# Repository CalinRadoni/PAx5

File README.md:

# PAx5

## Note

This repository is archived because I am building a version with better integration
in the [pax-devices](https://github.com/CalinRadoni/pax-devices) repository.

## Description

__PAx5__ is a home automation platform designed to be secure, stable and powerful.

__#__ Hardware is centered around an ultra-low-power ARM Cortex-M0+ and a sub-GHz radio.

__#__ For security:
- AEAD (_Authenticated Encryption with Associated Data_) using the 128 or 256 bits key ChaCha20 algorithm (the _new_ protocol used in HTTPS, TLS, OpenSSL, ...);
- Unique, random, session keys;
- Communication protocol designed to withstand the known attacks against these type of communications.

__#__ Stability is increased with:
- the radio module's power is generally enough to not require intermediary routers;
- designed for high availability, redundant, gateways.

### Dependencies

CMSIS

### Hardware details

MCU: STM32L051xx
Radio: RFM69HW
SPI FLASH Memory

Rendering and pinouts are in `Docs/PAx5_Base` and in `Docs/PAx5_EnvSensor`.

Environment sensor rendering:

and a photo of the sensor and base board:

### Development Environment

Main tools used are:
- [KiCad EDA](http://kicad-pcb.org/)
- [Atollic TrueSTUDIO](https://atollic.com/truestudio/) Free Edition
- [Atom](https://atom.io/) editor

Supplementary tools:
- [Git](https://git-scm.com/)
- [STM32CubeMX](http://www.st.com/en/development-tools/stm32cubemx.html)
- [Inkscape](https://inkscape.org/en/)

### License

PAx5's software and documentation is released under the [GNU GPLv3](http://www.gnu.org/licenses/gpl-3.0.html) License. See the __LICENSE-GPLv3.txt__ file.

PAx5's hardware schematics are licensed under a [Creative Commons Attribution-ShareAlike 4.0 International License](http://creativecommons.org/licenses/by-sa/4.0/).
See the __LICENSE-CC-BY-SA-4.0.txt__ file.

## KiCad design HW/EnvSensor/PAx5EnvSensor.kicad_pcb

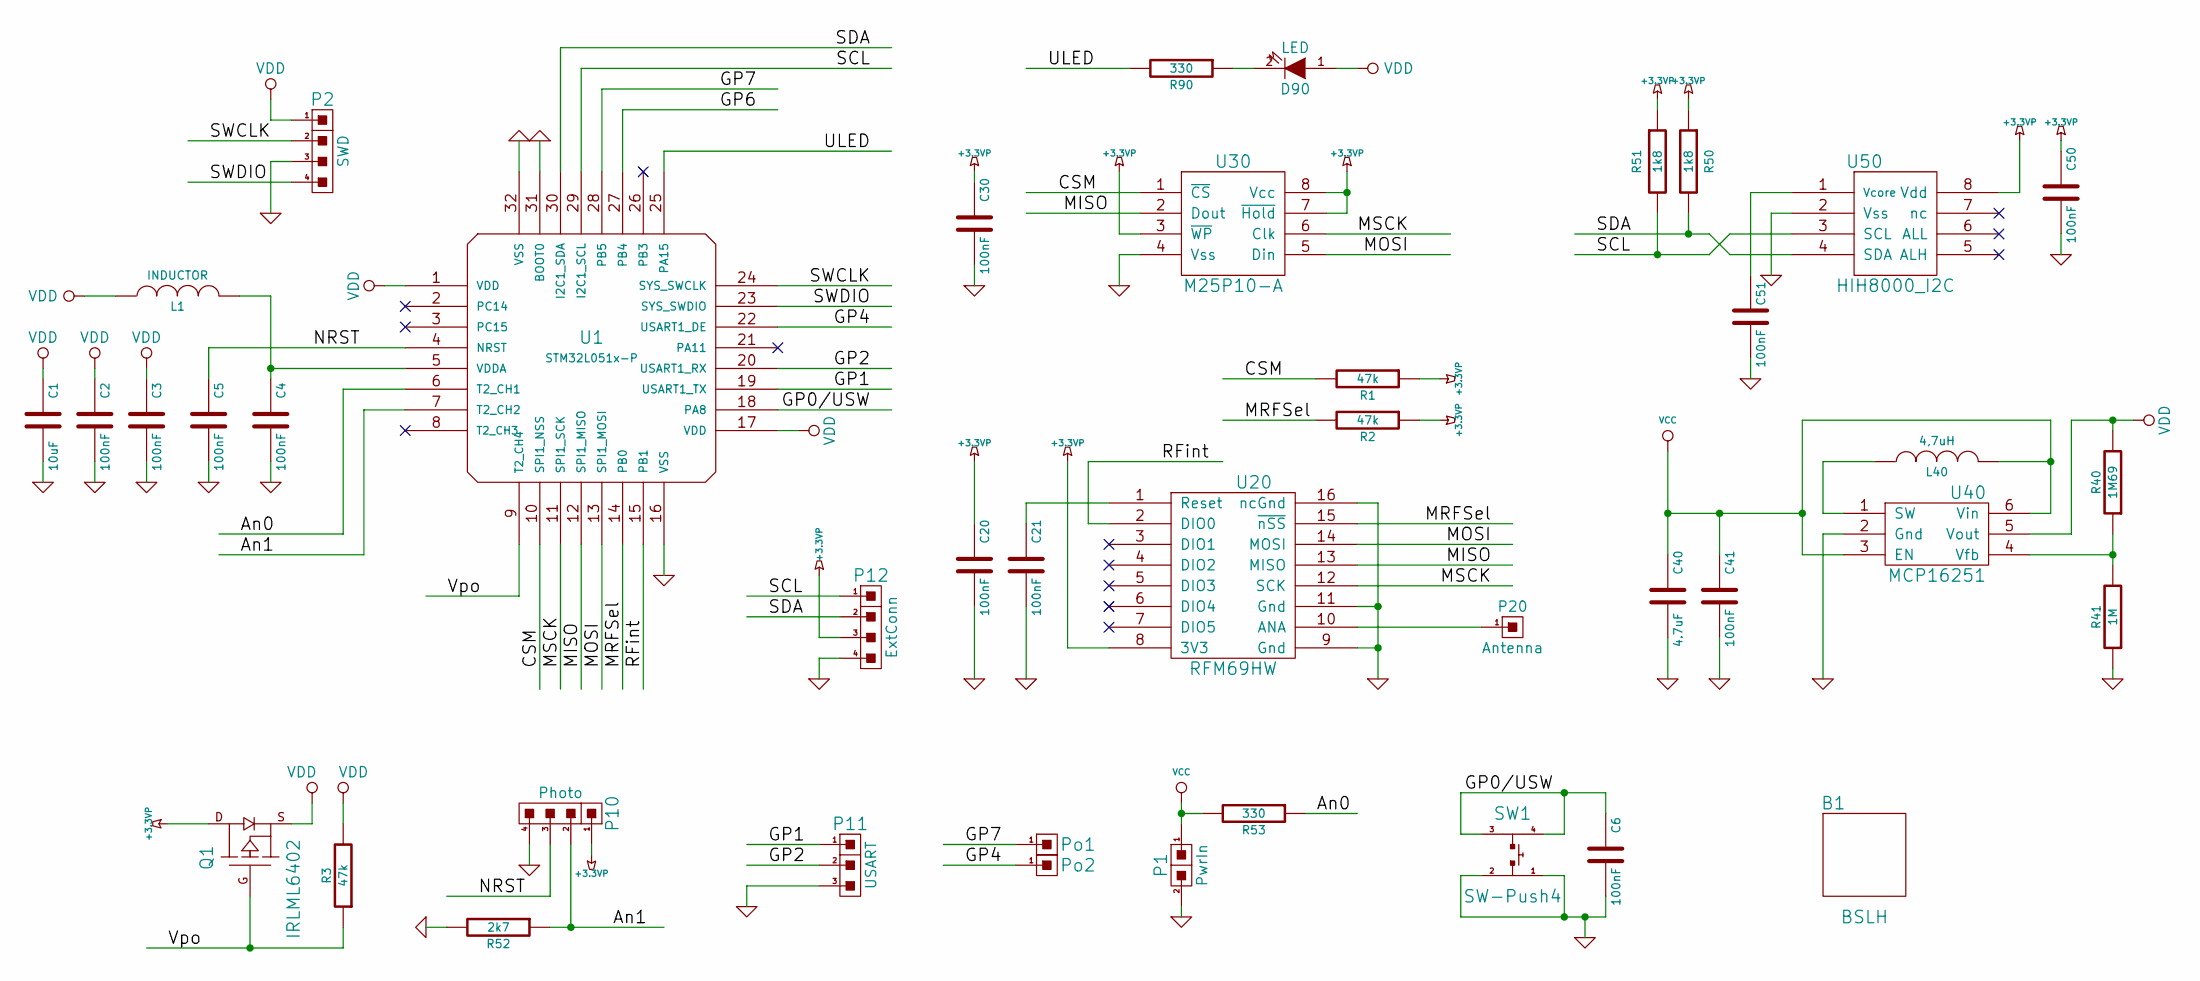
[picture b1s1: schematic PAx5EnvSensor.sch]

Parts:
B1: BSLH; Box-Sens-LH-NPTH
C1: 10uF; C_0805_HandSoldering
C2, C3, C4, C5, C6, C20, C21, C30, C41, C50, C51: 100nF; C_0805_HandSoldering
C40: 4.7uF; C_0805_HandSoldering
D90: LED; LED_1206_HandSoldering
L1: INDUCTOR; R_1206_HandSoldering
L40: 4,7uH; TYS50xx
P1: PwrIn; Pin_Header_Straight_1x02
P2: SWD; Pin_Header_Straight_1x04
P10: Photo; Pin_Header_Straight_1x04
P11: USART; Pin_Header_Straight_1x03
P12: ExtConn; Pin_Header_Straight_1x04
P20: Antenna; Pin_Header_Straight_1x01
Po1, Po2: PinTest-SMD
Q1: IRLML6402; SOT-23-calin
R1, R2, R3: 47k; R_0805_HandSoldering
R40: 1M69; R_0805_HandSoldering
R41: 1M; R_0805_HandSoldering
R50, R51: 1k8; R_0805_HandSoldering
R52: 2k7; R_1206_HandSoldering
R53: 330; R_0805_HandSoldering
R90: 330; R_1206_HandSoldering
SW1: SW-Push4; cSW-Push-4
U1: STM32L051x-P; cLQFP32-7-v2
U20: RFM69HW
U30: M25P10-A; SOIC-8-N
U40: MCP16251; SOT23-6
U50: HIH8000_I2C; HIH8000

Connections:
+3.3VP: C20.1, C30.1, C50.1, P10.1, P12.3, Q1.D, R1.1, R2.1, R50.1, R51.1, U20.8 (3V3), U30.3 (~WP), U30.7 (~Hold), U30.8 (Vcc), U50.8 (Vdd)
/An0: R53.1, U1.6 (T2_CH1)
/An1: P10.2, R52.1, U1.7 (T2_CH2)
/CSM: R1.2, U1.10 (SPI1_NSS), U30.1 (~CS)
/GP0/USW: C6.1, SW1.3, SW1.4, U1.18 (PA8)
/GP1: P11.1, U1.19 (USART1_TX)
/GP2: P11.2, U1.20 (USART1_RX)
/GP4: Po2.1, U1.22 (USART1_DE)
/GP7: Po1.1, U1.28 (PB5)
/MISO: U1.12 (SPI1_MISO), U20.13 (MISO), U30.2 (Dout)
/MOSI: U1.13 (SPI1_MOSI), U20.14 (MOSI), U30.5 (Din)
/MRFSel: R2.2, U1.14 (PB0), U20.15 (~nSS)
/MSCK: U1.11 (SPI1_SCK), U20.12 (SCK), U30.6 (Clk)
/NRST: C5.1, P10.3, U1.4 (NRST)
/RFint: U1.15 (PB1), U20.2 (DIO0)
/SCL: P12.1, R51.2, U1.29 (I2C1_SCL), U50.3 (SCL)
/SDA: P12.2, R50.2, U1.30 (I2C1_SDA), U50.4 (SDA)
/SWCLK: P2.2, U1.24 (SYS_SWCLK)
/SWDIO: P2.4, U1.23 (SYS_SWDIO)
/ULED: R90.2, U1.25 (PA15)
/Vpo: Q1.G, R3.1, U1.9 (T2_CH4)
GND: C1.2, C2.2, C3.2, C4.2, C5.2, C6.2, C20.2, C21.2, C30.2, C40.2, C41.2, C50.2, C51.2, P1.2, P2.3, P10.4, P11.3, P12.4, R41.1, R52.2, SW1.1, SW1.2, U1.16 (VSS), U1.31 (BOOT0), U1.32 (VSS), U20.9 (Gnd), U20.11 (Gnd), U20.16 (ncGnd), U30.4 (Vss), U40.2 (Gnd), U50.2 (Vss)
unnamed: C4.1, L1.2, U1.5 (VDDA)
unnamed: C21.1, U20.1 (Reset)
unnamed: C51.1, U50.1 (Vcore)
unnamed: D90.2 (K), R90.1
unnamed: L40.1, U40.1 (SW)
unnamed: P20.1, U20.10 (ANA)
unnamed: R40.1, R41.2, U40.4 (Vfb)
VCC: C40.1, C41.1, L40.2, P1.1, R53.2, U40.3 (EN), U40.6 (Vin)
VDD: C1.1, C2.1, C3.1, D90.1 (A), L1.1, P2.1, Q1.S, R3.2, R40.2, U1.1 (VDD), U1.17 (VDD), U40.5 (Vout)

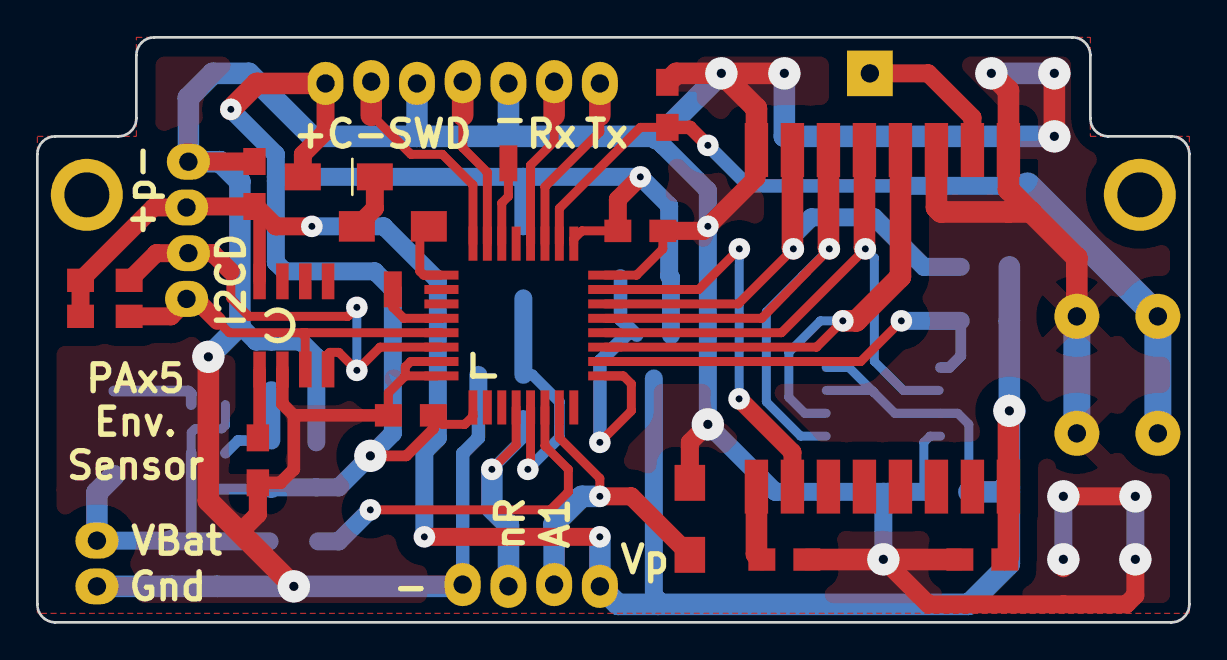
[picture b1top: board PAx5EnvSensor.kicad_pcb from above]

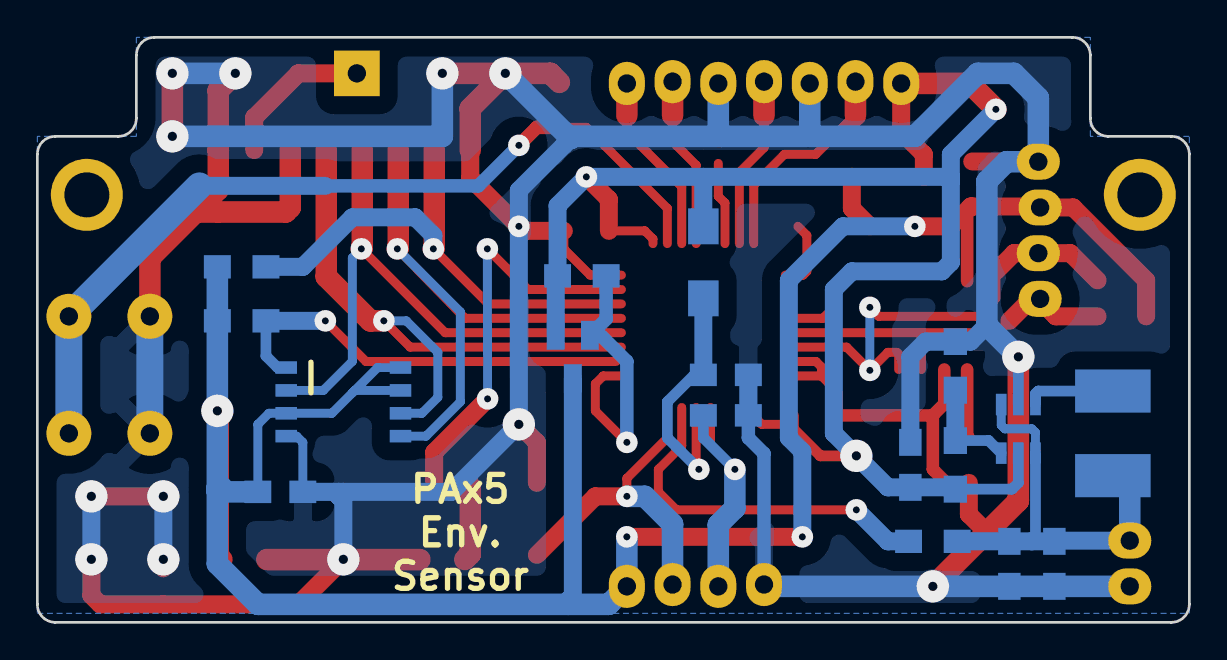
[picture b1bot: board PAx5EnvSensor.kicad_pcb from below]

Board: 2 copper layers, 64.0 x 32.5 mm, 42 parts (17 on the bottom side), 31 nets.

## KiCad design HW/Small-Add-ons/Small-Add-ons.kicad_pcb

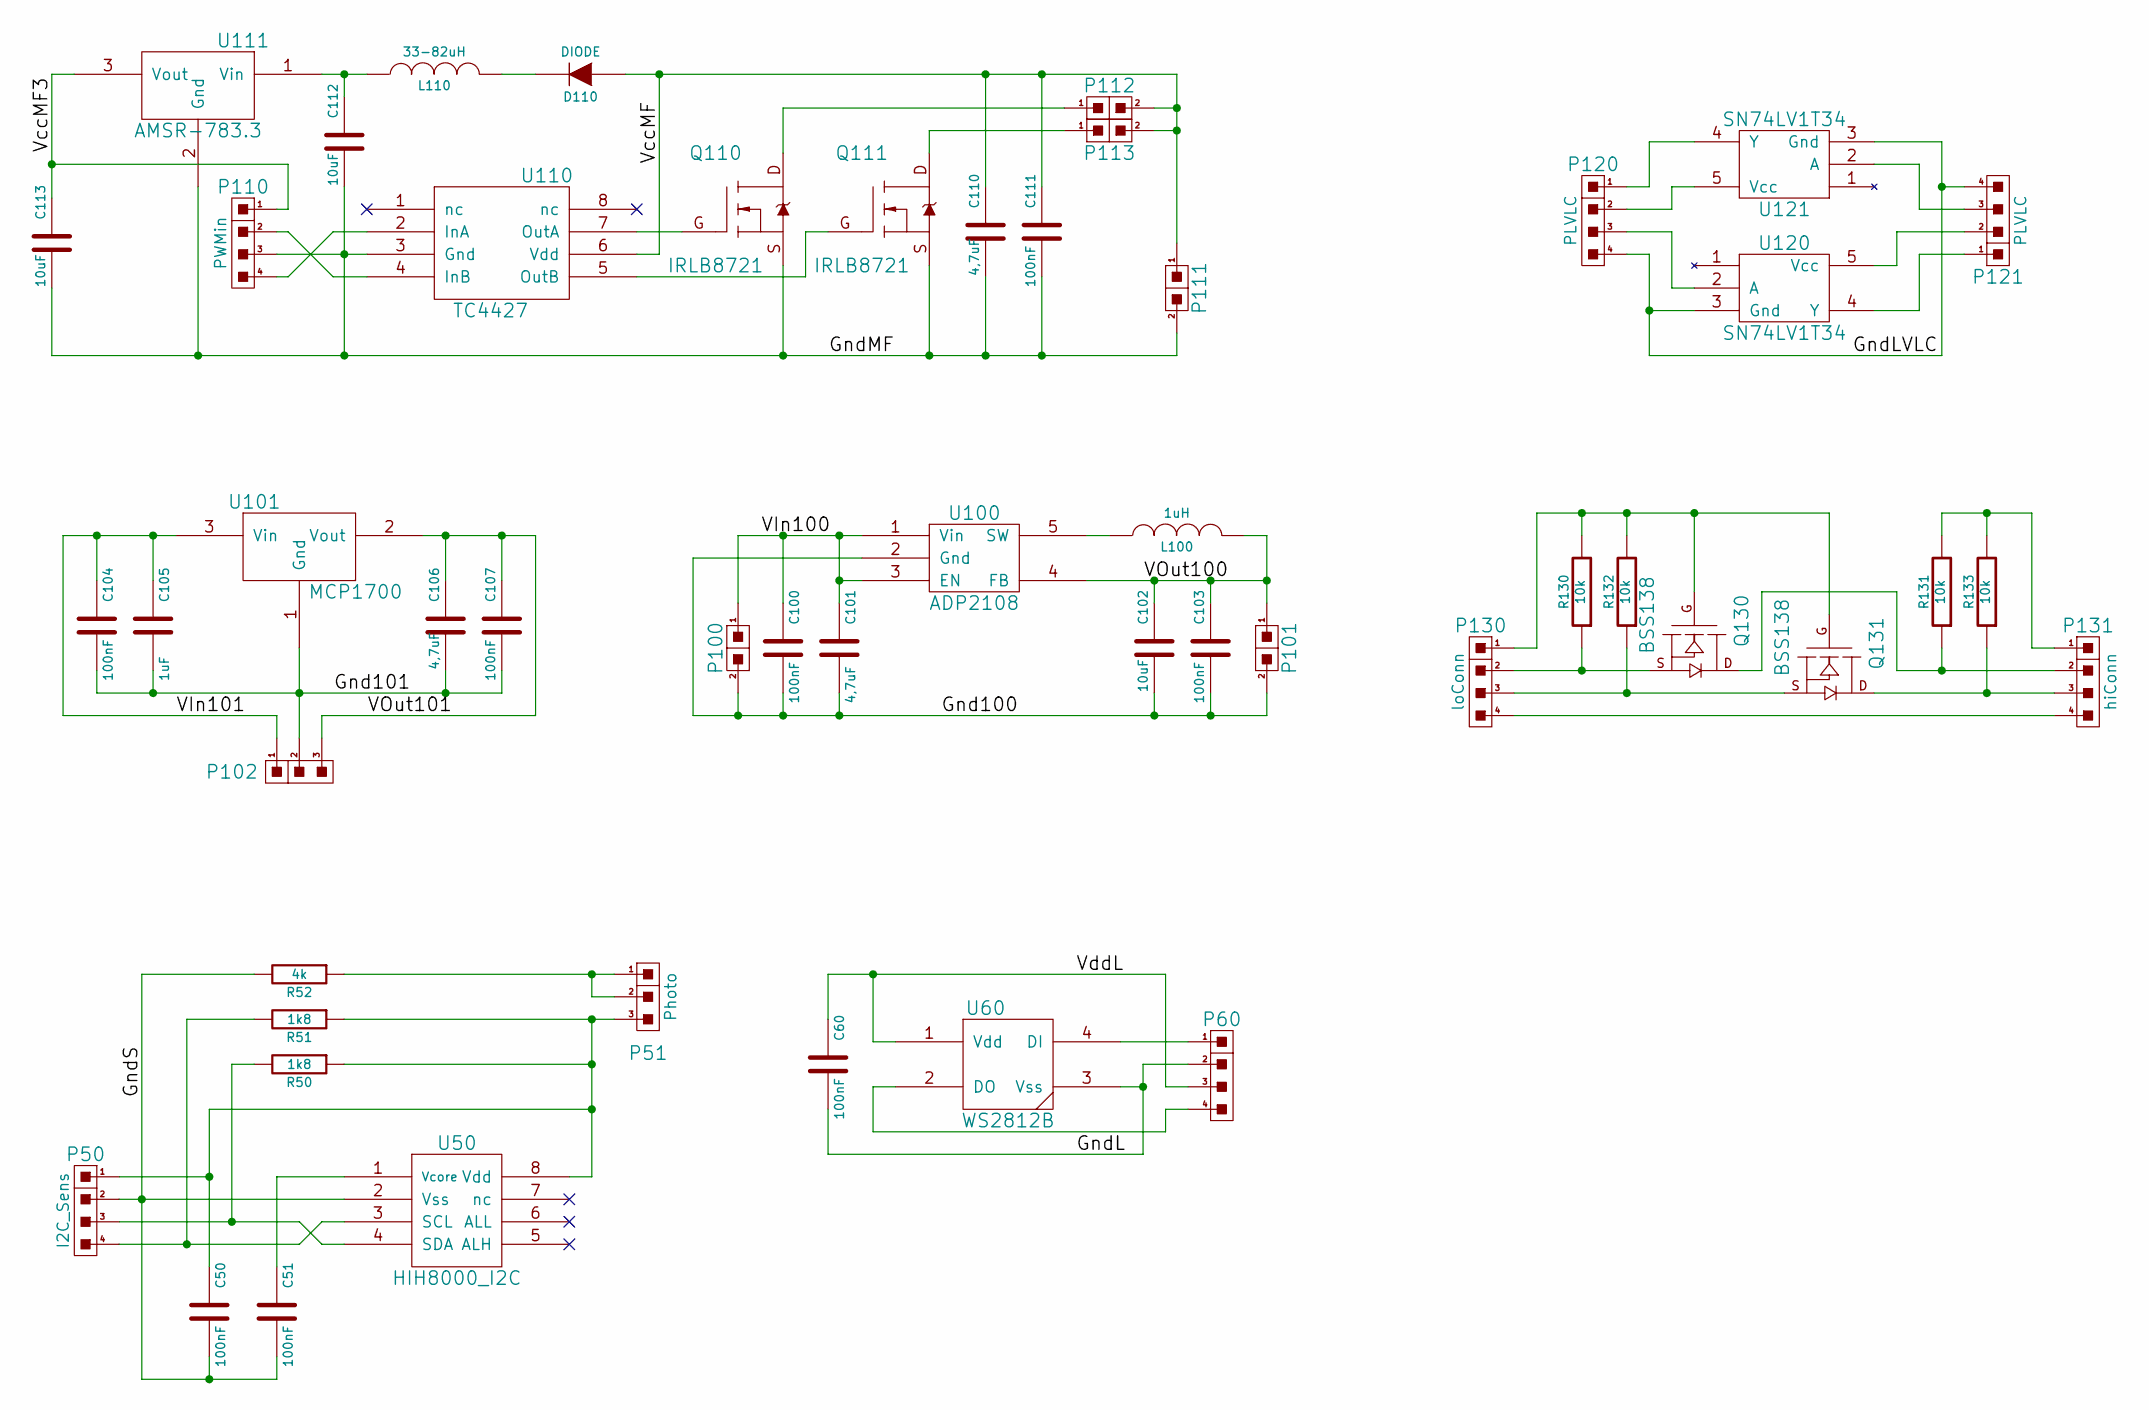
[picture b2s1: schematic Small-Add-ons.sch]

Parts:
C50, C51, C60, C100, C103, C104, C107, C111: 100nF; C_0805_HandSoldering
C101, C106, C110: 4,7uF; C_0805_HandSoldering
C102: 10uF; C_0805_HandSoldering
C105: 1uF; C_0805_HandSoldering
C112, C113: 10uF; C_1206_HandSoldering
D110: DIODE; DO-214AA-12
L100: 1uH; muRata-LQM2HPN1R0MJ0
L110: 33-82uH; COIL0608-0.033
P50: I2C_Sens; Pin_Header_Straight_1x04
P51: Photo; Pin_Header_Straight_1x03
P60: Pin_Header_Straight_1x04
P100: PVIn; Pin_Header_Straight_1x02
P101: PVOut; Pin_Header_Straight_1x02
P102: Pin_Header_Straight_1x03
P110: PWMin; Pin_Header_Straight_1x04
P111, P112, P113: PVOut; bornier2
P120, P121: PLVLC; Pin_Header_Straight_1x04
P130: loConn; Pin_Header_Straight_1x04
P131: hiConn; Pin_Header_Straight_1x04
Q110, Q111: IRLB8721; TO-220AB-GDS
Q130, Q131: BSS138; SOT-23-calin
R50, R51: 1k8; R_0805_HandSoldering
R52: 4k; R_1206_HandSoldering
R130, R131, R132, R133: 10k; R_0805_HandSoldering
U50: HIH8000_I2C; HIH8000
U60: WS2812B
U100: ADP2108; SOT23-5
U101: MCP1700; SOT23
U110: TC4427; SOIC-8-N
U111: AMSR-783.3; TO-220AB(SOT78)
U120, U121: SN74LV1T34; SOT23-5

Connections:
/Gnd100: C100.2, C101.2, C102.2, C103.2, P100.2, P101.2, U100.2 (Gnd)
/Gnd101: C104.2, C105.2, C106.2, C107.2, P102.2, U101.1 (Gnd)
/GndL: C60.2, P60.2, U60.3 (Vss)
/GndLVLC: P120.4, P121.4, U120.3 (Gnd), U121.3 (Gnd)
/GndMF: C110.2, C111.2, C112.2, C113.2, P110.3, P111.2, Q110.S, Q111.S, U110.3 (Gnd), U111.2 (Gnd)
/GndS: C50.2, C51.2, P50.2, R52.2, U50.2 (Vss)
/VIn100: C100.1, C101.1, P100.1, U100.1 (Vin), U100.3 (EN)
/VIn101: C104.1, C105.1, P102.1, U101.3 (Vin)
/VOut100: C102.1, C103.1, L100.2, P101.1, U100.4 (FB)
/VOut101: C106.1, C107.1, P102.3, U101.2 (Vout)
/VccMF: C110.1, C111.1, D110.1 (A), P111.1, P112.2, P113.2, U110.6 (Vdd)
/VccMF3: C113.1, P110.1, U111.3 (Vout)
/VddL: C60.1, P60.3, U60.1 (Vdd)
unnamed: C50.1, P50.1, P51.3, R50.1, R51.1, U50.8 (Vdd)
unnamed: C51.1, U50.1 (Vcore)
unnamed: C112.1, L110.1, U111.1 (Vin)
unnamed: D110.2 (K), L110.2
unnamed: L100.1, U100.5 (SW)
unnamed: P50.3, R50.2, U50.4 (SDA)
unnamed: P50.4, R51.2, U50.3 (SCL)
unnamed: P51.1, P51.2, R52.1
unnamed: P60.1, U60.4 (DI)
unnamed: P60.4, U60.2 (DO)
unnamed: P110.2, U110.4 (InB)
unnamed: P110.4, U110.2 (InA)
unnamed: P112.1, Q110.D
unnamed: P113.1, Q111.D
unnamed: P120.1, U121.4 (Y)
unnamed: P120.2, U121.5 (Vcc)
unnamed: P120.3, U120.2 (A)
unnamed: P121.1, U120.4 (Y)
unnamed: P121.2, U120.5 (Vcc)
unnamed: P121.3, U121.2 (A)
unnamed: P130.1, Q130.G, Q131.G, R130.2, R132.2
unnamed: P130.2, Q130.S, R130.1
unnamed: P130.3, Q131.S, R132.1
unnamed: P130.4, P131.4
unnamed: P131.1, R131.2, R133.2
unnamed: P131.2, Q130.D, R131.1
unnamed: P131.3, Q131.D, R133.1
unnamed: Q110.G, U110.7 (OutA)
unnamed: Q111.G, U110.5 (OutB)

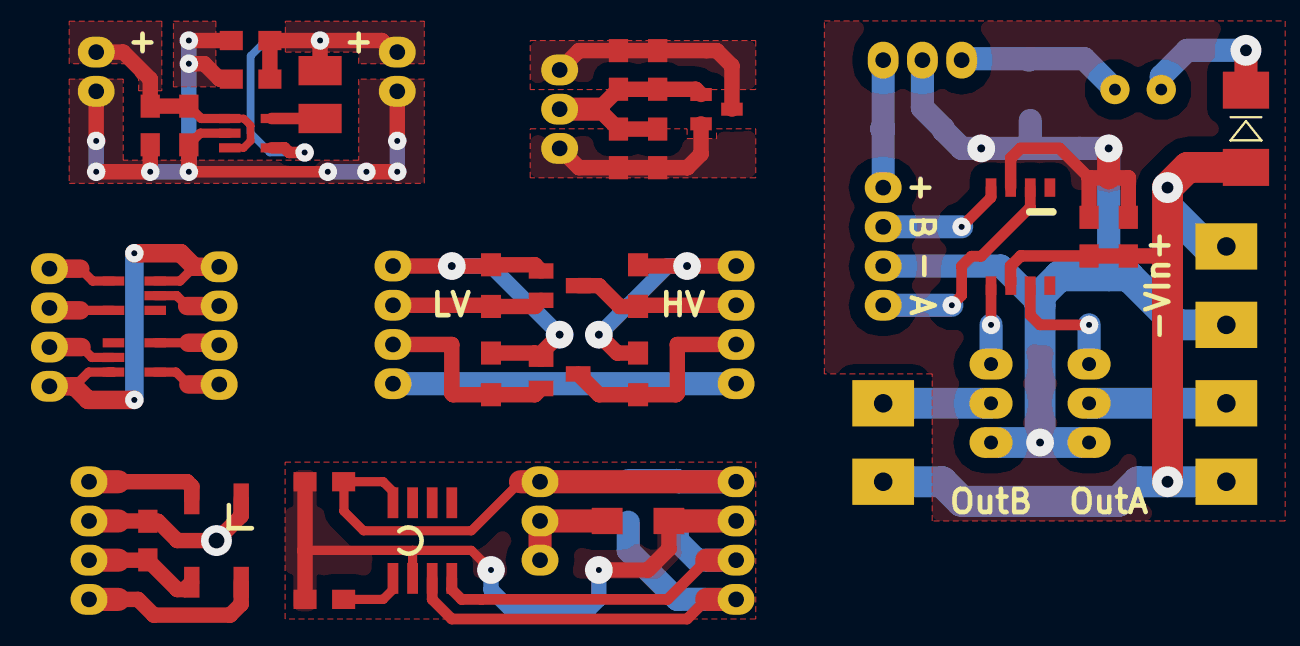
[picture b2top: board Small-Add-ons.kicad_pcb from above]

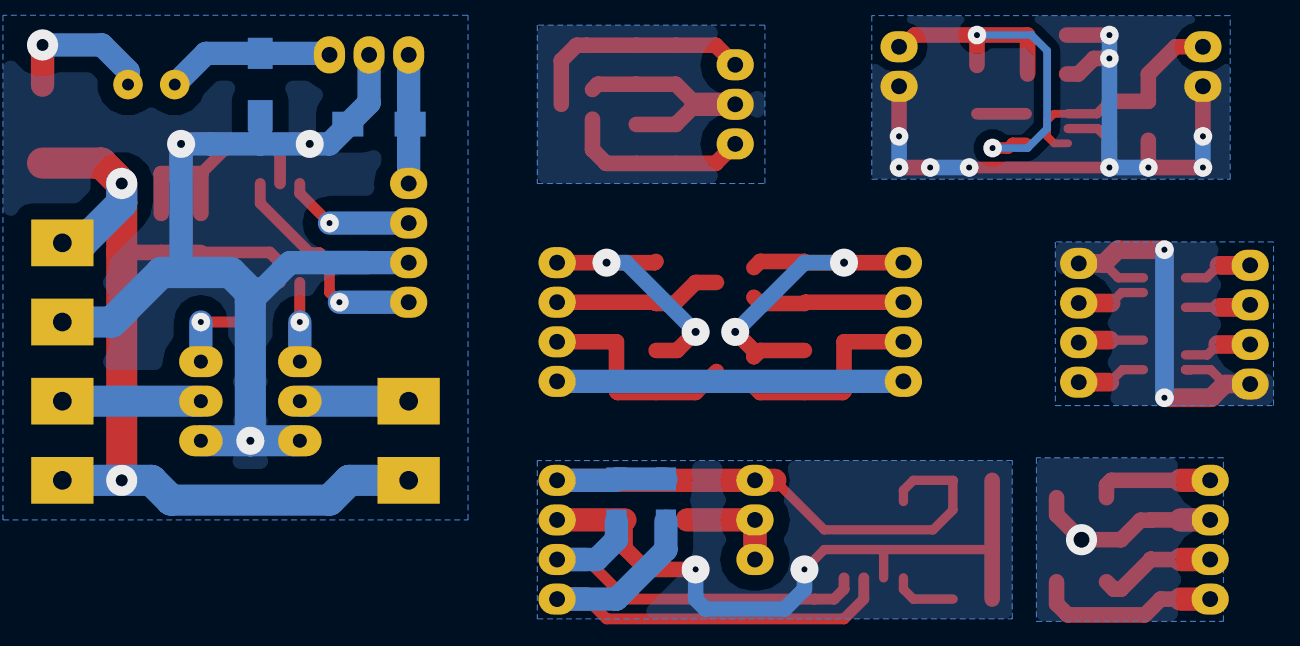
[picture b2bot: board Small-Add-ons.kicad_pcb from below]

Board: 2 copper layers, 51 parts (9 on the bottom side), 42 nets.

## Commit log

2017-05-03 Coding and commenting style update
2017-05-03 Refactoring of Comm directory
2017-05-29 License info added to .h and .cpp files and README update
2017-05-29 Improved the .gitattributes file
2017-06-01 Hints for linguist
2017-06-03 cpu_I2C update
2017-06-03 ext_WS2812 refactored to dev_WS2812
2017-06-03 refactored and updated
2017-06-03 small changes for clean compiling
2017-06-03 TSL2561 driver, not yet complete
2017-06-03 Updated .gitignore to exclude KiCad's autosave files
2017-06-04 dev_TSL2561 implemented
2017-06-04 dev_TSL2561 added clipping support and GetLux() example function
2017-06-05 reconfigured for BuildNumberInc
2017-06-06 corrected and tested WriteAndRead function for I2C repeated start
2017-06-06 dev_TSL2561 tested OK
2017-06-06 Formatting
2017-06-11 sCPU renamed to sCPUInfo
2017-06-11 Added CPU_Core to handle clock and power modules
2017-06-11 .gitattributes update
2017-06-12 Added push button handling code
2017-06-14 Added CPU_RTC for basic RTC and wake up timer functions
2017-06-18 Corrected CPU_Core, created a test function for CPU_Core and wake up timer (in CPU_RTC). Sleep, Stop and Standby mode tested OK.
2017-06-18 Corrected usage of \detail instead of \details in comments.
2017-06-19 Atollic TrueSTUDIO upgraded to 7.1.2
2017-06-27 Added flexible clock configuration, rebuilded and tested.
2017-07-21 Added a photo with the sensor and the base board.
2017-10-15 Added pin names for level convertor board
2017-10-15 no changes, Atollic TrueSTUDIO changed env-hash for com.atollic.truestudio.mbs.GCCSpecsDetectorAtollicArm class
2017-10-15 RTC prescaler changed to create 1 Hz RTC clock from LSI oscillator. Improved doc from involved files and updated the test code.
2019-09-22 Archiving the repository
